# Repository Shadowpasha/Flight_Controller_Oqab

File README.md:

# Flight_Controller_Oqab

ESP32-based modular flight controller for multirotor UAVs and quadcopters (Quad-X configuration). Features a 250 Hz deterministic attitude loop, 50 Hz altitude/horizontal Kalman filtering, 10 Hz GPS dead reckoning navigation, and runtime-selectable control algorithms.

## 🚀 Key Features

* **Multi-Algorithm Attitude Controllers**:
  * **PID**: Cascaded Angle (P) & Rate (PID) loops.
  * **SMC**: Sliding Mode Control with boundary layer.
  * **ADRC**: Linear Active Disturbance Rejection Control (LADRC with ESO).
  * **MDBCI**: Modified Dual Boundary Conditional Integration Backstepping (*ISA Transactions 2020*).
  * **MDBCIS**: MDBCI + Jerk-Mitigating Switched Controller.
  * **VIABC**: Variable Integral Adaptive Backstepping (*IEEE Access 2024*).
  * **CDI / CVI / NOI**: Conditional, Conventional, and No-Integration Backstepping variants.
* **Sensor Suite**:
  * **IMU**: MPU6050 (6-DOF Accelerometer + Gyroscope) at 250 Hz.
  * **Optical Flow & ToF LiDAR**: Mateksys 3901-L0X / 3901-L1X via MSPv2 on UART2 (RX=16, TX=17 @ 115200 baud) for gyro-derotated horizontal velocity and primary altitude estimation.
  * **Barometer & Compass**: BMP180 / GY-87 (QMC5883P / HMC5883L) via I2C.
  * **GPS (Optional)**: NEO-6M / NEO-7M / NEO-M8N / BN-220 via TinyGPS++ on UART2.
* **PX4-Style Outer Control & Flight Management**:
  * **Altitude & Hover**: 50 Hz Z position P -> velocity PID (`MPC_Z_CLIMB = 0.18 m/s`, `MPC_Z_DESC = 0.35 m/s`), bumpless liftoff handoff (`MPC_THR_HOVER = 1450 us`, `TAKEOFF_THROTTLE = 1480 us`), and toggleable in-flight hover learning (`MPC_HOVER_LEARN`).
  * **Separate Descent Rates**: Normal landing (`land` / hover timeout) at `MPC_RAMP_DN = 35 us/s` (12 cm/s) and emergency fast landing (`start` toggle in flight / `stop` / ceiling guard) at `MPC_RAMP_EMG = 100 us/s` (40 cm/s).
  * **Gentle F330 Position Hold**: Optical flow position hold activates once airborne above `POS_HOLD_MIN_AGL_CM` (9.0 cm over ground) with gentle F330 defaults (`MPC_XY_P = 0.60`, `MPC_XY_VEL_P = 1.50`, `MPC_XY_MAX_TILT = 4.0 deg`).
* **Communications, Telemetry & Dashboard**:
  * **USB Serial & Classic Bluetooth SPP** (`BluetoothSerial`, device name: `Oqab_Flight_Controller`).
  * Live dead-reckoning telemetry stream and interactive CLI for runtime tuning, arming, mode switching, and Flash NVS parameter management.
  * Companion **Tauri/React Dashboard** in `dashboard/` for 3D attitude visualization, live telemetry charting, and flow derotation inspection.

## 🔌 Pin Configuration

| Component | Pin (ESP32) | Notes |
| :--- | :--- | :--- |
| **ESC 1 (Front Right, CCW)** | GPIO 14 | 250 Hz PWM |
| **ESC 2 (Rear Right, CW)** | GPIO 27 | 250 Hz PWM |
| **ESC 3 (Rear Left, CCW)** | GPIO 26 | 250 Hz PWM |
| **ESC 4 (Front Left, CW)** | GPIO 25 | 250 Hz PWM |
| **Sharp IR Distance** | GPIO 34 | ADC1 Channel 6 |
| **GPS RX** | GPIO 16 | Connects to GPS TX (9600 baud) |
| **GPS TX** | GPIO 17 | Connects to GPS RX |
| **I2C SDA / SCL** | GPIO 21 / 22 | IMU, Baro, Compass |

## 🛠 Project Structure

```text
balance_controller/
├── balance_controller.ino  # Main setup, loop scheduler, and state machine
├── Config.h                # Hardware pinouts, loop timing, safety ceilings
├── FlightState.h           # Drone state, mission stages, sensor data structs
├── Controllers.h / .cpp    # PID, SMC, ADRC, Backstepping implementations
├── StateEstimator.h / .cpp # Attitude filter, 3-state altitude EKF, GPS projection
├── Sensors.h / .cpp        # Modular hardware drivers (MPU6050, Sharp, BMP, Compass, GPS)
├── Motors.h / .cpp         # ESC signal generation and Quad-X motor mixer
├── Comms.h / .cpp          # Serial/Bluetooth telemetry and interactive CLI
├── Parameters.h / .cpp     # Non-volatile parameter storage (NVS / Flash)
└── tools/
    ├── test_gps/           # Standalone 1 Hz GPS telemetry & auto-baud tool
    ├── recover_gps/        # U-blox factory reset & NMEA 9600 baud restoration script
    └── test_bluetooth/     # Standalone ESP32 Bluetooth Classic SPP test script
```

## 💻 Quick Start

1. Open `balance_controller/balance_controller.ino` in the Arduino IDE.
2. Select your ESP32 board (`ESP32 Dev Module`).
3. Compile and flash via USB.
4. Open the Serial Monitor (or connect via Bluetooth Terminal) at **115200 baud**.
5. Available CLI commands:
   * `arm` / `disarm` - Motor control toggle
   * `start` - Arm & begin autonomous takeoff/hover/land mission; send `start` again in flight for emergency fast landing (`MPC_RAMP_EMG`, 100 us/s)
   * `land` / `stop` - Normal controlled descent (`MPC_RAMP_DN`, 35 us/s) vs emergency landing (`stop`)
   * `hover learn <on|off>` - Enable or disable automatic hover throttle learning (`MPC_HOVER_LEARN`)
   * `ctrl <pid|smc|adrc|mdbci|mdbcis|viabc>` - Switch active attitude controller
   * `flow <on|off|toggle>` / `gps <on|off|toggle>` - Enable or disable Optical Flow / GPS subsystems (saved to Flash)
   * `status` - Full flight controller health report
   * `param show` / `param set <NAME> <VAL>` / `param reset` - Inspect, update, or reset Flash NVS parameters

See [docs/oqab_control_estimation_architecture.tex](docs/oqab_control_estimation_architecture.tex) for the full mathematical model, state machine, and estimator equations.

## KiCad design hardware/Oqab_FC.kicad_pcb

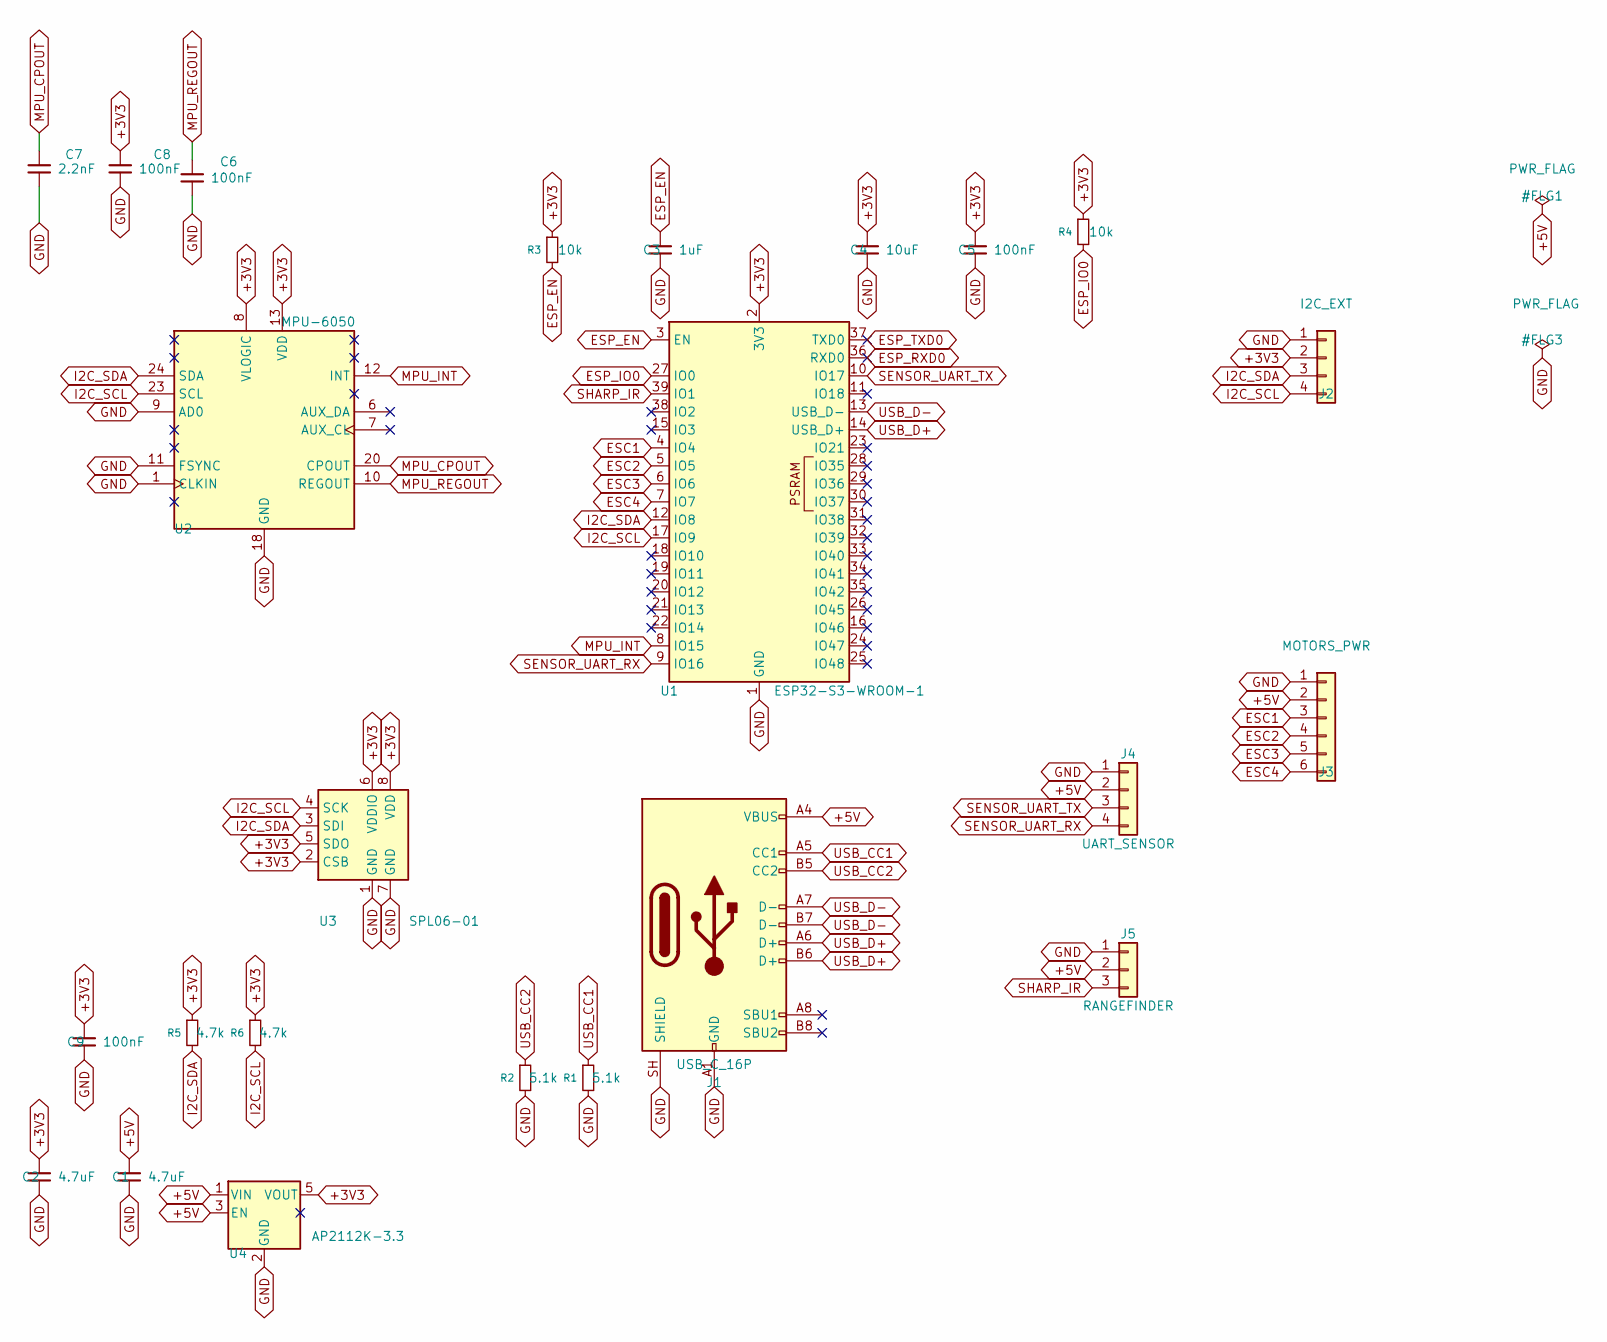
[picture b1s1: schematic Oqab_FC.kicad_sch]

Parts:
C1, C2: 4.7uF; C_0603_1608Metric
C3: 1uF; C_0603_1608Metric
C4: 10uF; C_0603_1608Metric
C5, C6, C8, C9: 100nF; C_0603_1608Metric
C7: 2.2nF; C_0603_1608Metric
J1: USB_C_16P; USB_C_Receptacle_HRO_TYPE-C-31-M-12
J2: I2C_EXT; PinHeader_1x04_P2.54mm_Vertical
J3: MOTORS_PWR; PinHeader_1x06_P2.54mm_Vertical
J4: UART_SENSOR; PinHeader_1x04_P2.54mm_Vertical
J5: RANGEFINDER; PinHeader_1x03_P2.54mm_Vertical
R1, R2: 5.1k; R_0603_1608Metric
R3, R4: 10k; R_0603_1608Metric
R5, R6: 4.7k; R_0603_1608Metric
U1: ESP32-S3-WROOM-1
U2: MPU-6050; InvenSense_QFN-24_4x4mm_P0.5mm
U3: SPL06-01; Bosch_LGA-8_2x2.5mm_P0.65mm_ClockwisePinNumbering
U4: AP2112K-3.3; SOT-23-5

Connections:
+3V3: C2.1, C4.1, C5.1, C8.1, C9.1, J2.2, R3.1, R4.1, R5.1, R6.1, U1.2 (3V3), U2.8 (VLOGIC), U2.13 (VDD), U3.2 (CSB), U3.5 (SDO), U3.6 (VDDIO), U3.8 (VDD), U4.5 (VOUT)
+5V: C1.1, J1.A4 (VBUS), J1.A9 (VBUS), J1.B4 (VBUS), J1.B9 (VBUS), J3.2, J4.2, J5.2, U4.1 (VIN), U4.3 (EN)
ESC1: J3.3, U1.4 (IO4)
ESC2: J3.4, U1.5 (IO5)
ESC3: J3.5, U1.6 (IO6)
ESC4: J3.6, U1.7 (IO7)
ESP_EN: C3.1, R3.2, U1.3 (EN)
ESP_IO0: R4.2, U1.27 (IO0)
ESP_RXD0: U1.36 (RXD0)
ESP_TXD0: U1.37 (TXD0)
GND: C1.2, C2.2, C3.2, C4.2, C5.2, C6.2, C7.2, C8.2, C9.2, J1.A1 (GND), J1.A12 (GND), J1.B1 (GND), J1.B12 (GND), J1.SH (SHIELD), J2.1, J3.1, J4.1, J5.1, R1.2, R2.2, U1.1 (GND), U1.40 (GND), U1.41 (GND), U2.1 (CLKIN), U2.9 (AD0), U2.11 (FSYNC), U2.18 (GND), U3.1 (GND), U3.7 (GND), U4.2 (GND)
I2C_SCL: J2.4, R6.2, U1.17 (IO9), U2.23 (SCL), U3.4 (SCK)
I2C_SDA: J2.3, R5.2, U1.12 (IO8), U2.24 (SDA), U3.3 (SDI)
MPU_CPOUT: C7.1, U2.20 (CPOUT)
MPU_INT: U1.8 (IO15), U2.12 (INT)
MPU_REGOUT: C6.1, U2.10 (REGOUT)
SENSOR_UART_RX: J4.4, U1.9 (IO16)
SENSOR_UART_TX: J4.3, U1.10 (IO17)
SHARP_IR: J5.3, U1.39 (IO1)
USB_CC1: J1.A5 (CC1), R1.1
USB_CC2: J1.B5 (CC2), R2.1
USB_D+: J1.A6 (D+), J1.B6 (D+), U1.14 (USB_D+)
USB_D-: J1.A7 (D-), J1.B7 (D-), U1.13 (USB_D-)

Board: 2 copper layers, 28 parts (6 on the bottom side), 21 nets, no tracks yet.

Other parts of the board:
MH1, MH2, MH3, MH4: MountingHole_3.2mm

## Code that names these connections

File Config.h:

#ifndef CONFIG_H
#define CONFIG_H

#include <Arduino.h>

// =============================================================================
//  SYSTEM CONFIGURATION & TUNING CONSTANTS
// =============================================================================

// --- Controller Options ---
enum ControllerType {
  CONTROLLER_PID = 0,    // Standard Cascaded / Angle / Rate PID
  CONTROLLER_SMC = 1,    // Sliding Mode Control (SMC with boundary layer)
  CONTROLLER_ADRC = 2,   // Linear Active Disturbance Rejection Control (LADRC)
  CONTROLLER_MDBCI = 3,  // Modified Dual Boundary Conditional Integration Backstepping (ISA 2020 Eq. 44)
  CONTROLLER_MDBCIS = 4, // MDBCI + Jerk-Mitigating Switched Controller (ISA 2020 Section 4.2)
  CONTROLLER_CDI = 5,    // Conditional Integration Backstepping (Seshagiri & Khalil 2005)
  CONTROLLER_CVI = 6,    // Conventional Integral Backstepping (Constant lambda_m)
  CONTROLLER_NOI = 7,    // No-Integration Backstepping (lambda = 0)
  CONTROLLER_VIABC = 8,  // Variable Integral Adaptive Backstepping (IEEE Access 2024)
  CONTROLLER_BACKSTEPPING = CONTROLLER_MDBCI // Alias for convenience
};-

// Default active controller at boot (can also be switched at runtime via 'ctrl pid|smc|adrc|mdbci|mdbcis|cdi|cvi|noi|viabc')
#define DEFAULT_CONTROLLER CONTROLLER_PID

// --- Flight Modes ---
enum FlightMode {
  MODE_CASCADE = 0, // Outer Angle P -> Inner Rate Loop (Default)
  MODE_ANGLE   = 1, // Single-loop Angle Loop
  MODE_RATE    = 2  // Single-loop Rate Loop (Acro Mode)
};

// --- Auto-Flight Mission Stages ---
enum FlightStage {
  STAGE_IDLE = 0,
  STAGE_RAMP_UP,
  STAGE_HOVER,
  STAGE_LANDING,
  STAGE_TOUCHDOWN
};

// --- Active Altitude Sensor Source ---
enum AltSource {
  ALT_SOURCE_LIDAR = 0,
  ALT_SOURCE_SHARP,
  ALT_SOURCE_BARO_ACC
};

// --- Hardware Pin Definitions ---
// ESC Pins (Quad-X configuration)
#define ESC1_PIN 14 // Front Right (M1, CCW)
#define ESC2_PIN 27 // Rear Right  (M2, CW)
#define ESC3_PIN 26 // Rear Left   (M3, CCW)
#define ESC4_PIN 25 // Front Left  (M4, CW)
#define ESC_FREQ 250 // 250 Hz PWM refresh rate

// Distance & Compass / Baro Pins
#define SHARP_IR_PIN 34 // ADC1_CH6 analog input

// Sensor Serial2 Pins (Shared UART port for GPS or Matek Optical Flow)
#define SENSOR_UART_RX_PIN  16
#define SENSOR_UART_TX_PIN  17

// GPS Subsystem Toggle (Legacy)
#define USE_GPS             false // Set false to disable GPS entirely
#define GPS_RX_PIN          SENSOR_UART_RX_PIN
#define GPS_TX_PIN          SENSOR_UART_TX_PIN
#define GPS_BAUD            9600  // 9600 baud for NMEA

// Optical Flow Subsystem (Mateksys 3901-L0X / 3901-L1X via MSPv2)
#define USE_OPTICAL_FLOW    true   // Master toggle: Mateksys Optical Flow as primary horizontal estimator
#define FLOW_RX_PIN         SENSOR_UART_RX_PIN
#define FLOW_TX_PIN         SENSOR_UART_TX_PIN
#define FLOW_BAUD           115200 // Matek 3901 MSPv2 default baud rate
#define FLOW_RAD_PER_COUNT  0.0038f // PMW3901 42 deg FOV angular scale (rad/count)
#define FLOW_QUALITY_THRESH 35     // Minimum tracking quality threshold (0-255)
#define FLOW_MIN_HEIGHT_M   0.05f  // Minimum ground distance (5cm) for flow calculation
#define FLOW_MAX_HEIGHT_M   3.00f  // Maximum reliable range (3.0m)
#define FLOW_DEFAULT_ROT_DEG 0.0f  // Mounting yaw rotation in degrees: 0=Forward, 90=Right, 180=Rear, 270=Left

// Bluetooth Device Name
#define BT_DEVICE_NAME "F330_Flight_Controller"

// --- Loop Timing ---
#define LOOP_RATE_HZ         250
#define LOOP_PERIOD_US       4000     // 4000 us = 250 Hz
#define ALT_LOOP_PERIOD_MS   20       // 20 ms = 50 Hz
#define GPS_LOOP_PERIOD_MS   100      // 100 ms = 10 Hz

// --- Throttle & Safety Limits ---
#define MIN_ARMED_PWM        1080     // Idle spin floor
#define MAX_MOTOR_PWM        1920     // Ceiling giving headroom for differential control
#define PID_ACTIVE_THROTTLE  1200     // Closed loop starts early during takeoff
#define TAKEOFF_THROTTLE     1360     // Throttle threshold for airborne detection (~1360us)
#define MAX_TAKEOFF_RAMP_PWM 1500     // Upper safety ceiling for automatic liftoff climb ramp
#define THROTTLE_RAMP_RATE   40.0f    // Slow, ultra-smooth climb ramp rate (~40 us/s; ~6.5s from idle to liftoff)
#define LAND_RAMP_RATE       35.0f    // Gentle landing descent rate (~35 us/s)
#define MAX_TILT_ANGLE_DEG   40.0f    // Instant crash disarm threshold
#define TIMEOUT_SAFETY_MS    30000    // 30s safety watchdog without serial command

// --- Pure ToF LiDAR Altitude Control Config ---
#define USE_LIDAR_ONLY_ALTITUDE   true   // Lock vertical state estimation exclusively to Mateksys ToF LiDAR (0-200cm, immune to downwash/baro drift)
#define USE_SHARP_ONLY_ALTITUDE   false  // Legacy Sharp GP2Y0A analog IR rangefinder (dewired)
#define DEFAULT_TARGET_HEIGHT_CM  45.0f  // 45 cm hover height
#define MAX_SAFE_CEILING_CM       185.0f // Safety ceiling before Matek 3901-L0X VL53 ToF saturation (200cm) triggering emergency descent

// Output Saturation Caps
#define MAX_PID_OUT          350.0f   // Max differential PWM for roll/pitch
#define MAX_YAW_OUT          200.0f   // Max yaw differential PWM
#define MAX_TARGET_RATE      400.0f   // Max target rate in deg/s

#endif // CONFIG_H
